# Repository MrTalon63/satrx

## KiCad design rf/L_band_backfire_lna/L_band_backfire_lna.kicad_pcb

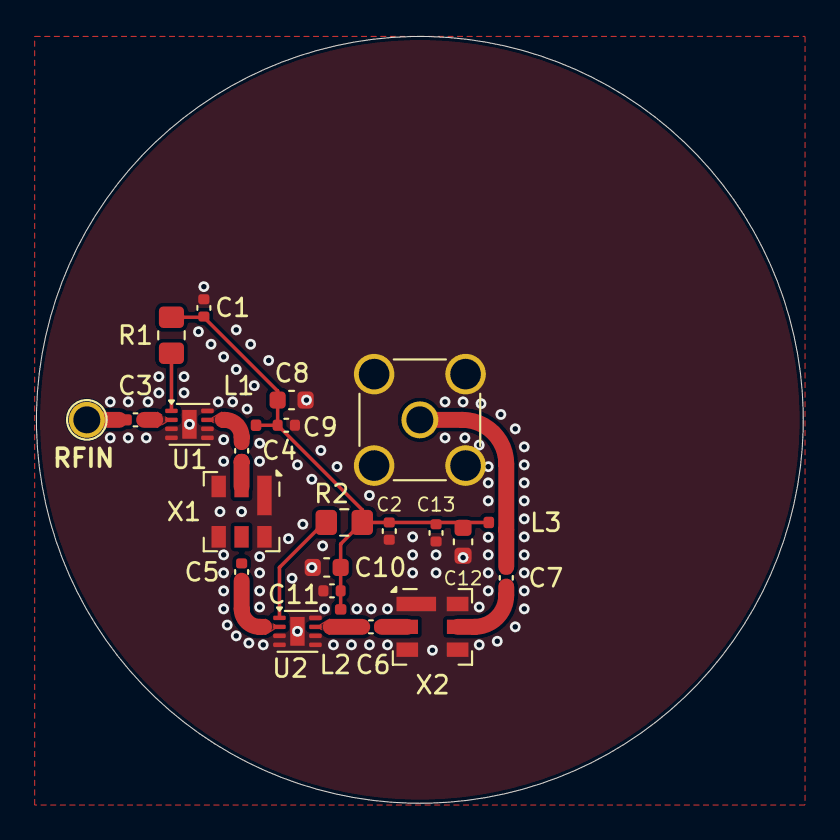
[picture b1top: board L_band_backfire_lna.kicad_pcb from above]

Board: 2 copper layers, 42.6 x 42.6 mm, 24 parts (0 on the bottom side), 14 nets.

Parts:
C1, C2, C3, C4, C5, C6, C7, C9, C11, C13: 100p; C_0402_1005Metric
C8, C10, C12: 100n; C_0603_1608Metric
J1: SMA; Special Hole
J2: SMA; SMA_Amphenol_901-144_Vertical
L1, L2, L3: 56n; L_0402_1005Metric
R1, R2: 3.32k; R_0805_2012Metric_Pad1.20x1.40mm_HandSolder
U1, U2: QPL9547; DFN-8-1EP_2x2mm_P0.5mm_EP0.8x1.6mm
X1, X2: SAW; Filter_SAW-6_3.8x3.8mm

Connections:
GND: C1.2, C2.2, C8.2, C9.1, C10.2, C11.1, C12.2, C13.1, J2.2 (Ext), U1.3 (GND), U1.4 (GND), U1.5 (GND), U1.6 (~EN), U1.8 (GND), U1.9 (GND), U2.3 (GND), U2.4 (GND), U2.5 (GND), U2.6 (~EN), U2.8 (GND), U2.9 (GND), X1.1 (GND), X1.3 (GND), X1.4 (GND), X1.6 (GND), X2.1 (GND), X2.3 (GND), X2.4 (GND), X2.6 (GND)
unnamed: C3.2, U1.2
unnamed: C4.1, L1.1, U1.7
unnamed: C5.2, U2.2
unnamed: C6.1, L2.1, U2.7
unnamed: C3.1, J1.1 (In)
unnamed: C7.2, J2.1 (In), L3.1
unnamed: R1.2, U1.1 (Vb)
unnamed: R2.2, U2.1 (Vb)
unnamed: C4.2, X1.2 (IN)
unnamed: C5.1, X1.5 (OUT)
unnamed: C6.2, X2.2 (IN)
unnamed: C7.1, X2.5 (OUT)
VCC: C1.1, C2.1, C8.1, C9.2, C10.1, C11.2, C12.1, C13.2, L1.2, L2.2, L3.2, R1.1, R2.1

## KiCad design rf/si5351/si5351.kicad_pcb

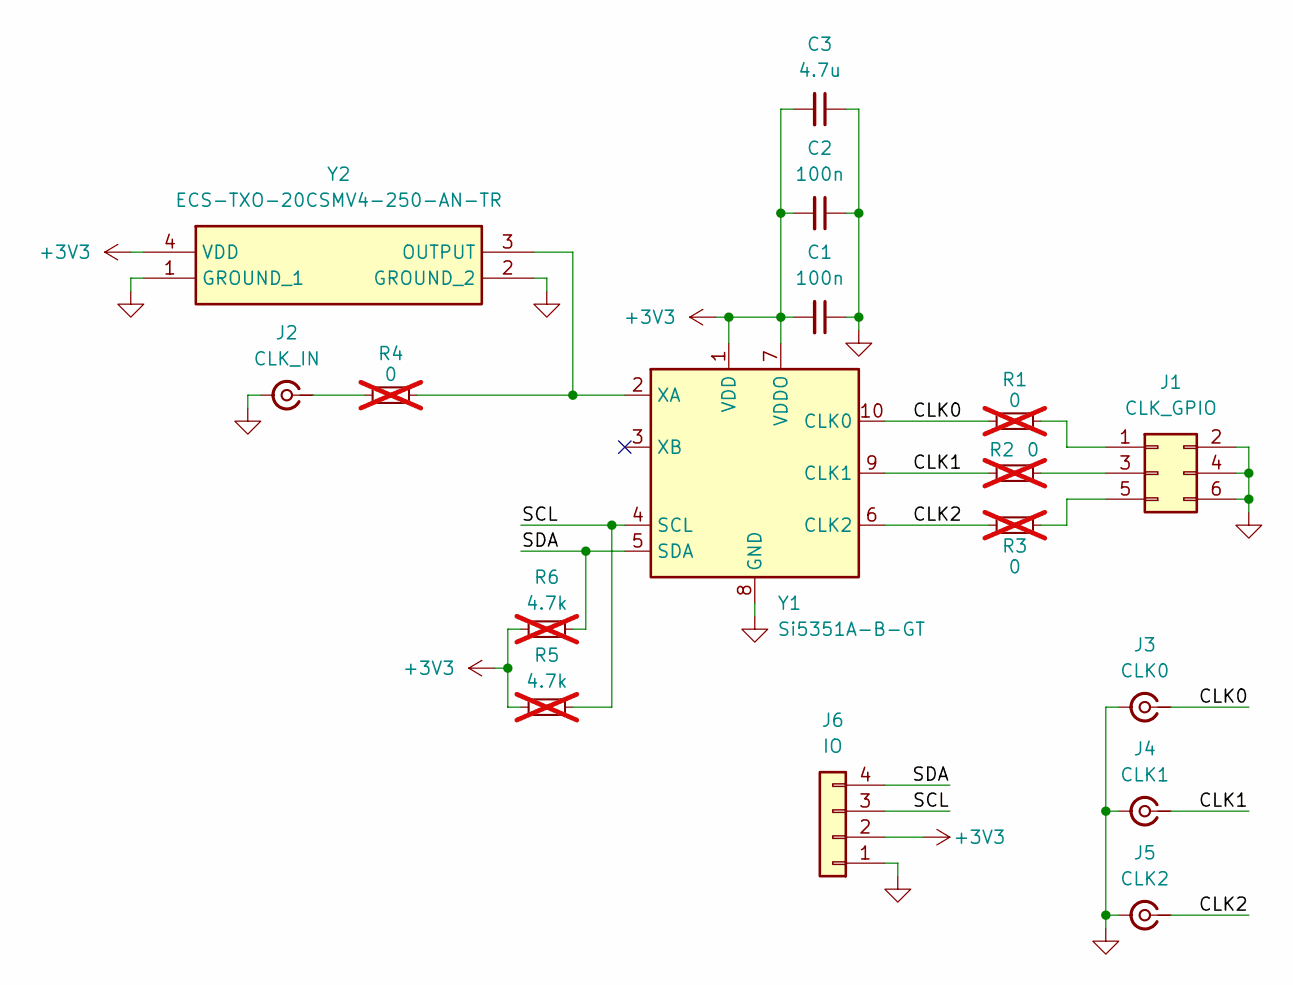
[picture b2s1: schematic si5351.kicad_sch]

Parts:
C1, C2: 100n; C_0603_1608Metric_Pad1.08x0.95mm_HandSolder
C3: 4.7u; C_0603_1608Metric_Pad1.08x0.95mm_HandSolder
J1: CLK_GPIO; PinHeader_2x03_P2.54mm_Vertical
J2: CLK_IN; SMA_Samtec_SMA-J-P-H-ST-EM1_EdgeMount
J3: CLK0; SMA_Samtec_SMA-J-P-H-ST-EM1_EdgeMount
J4: CLK1; SMA_Samtec_SMA-J-P-H-ST-EM1_EdgeMount
J5: CLK2; SMA_Samtec_SMA-J-P-H-ST-EM1_EdgeMount
J6: IO; PinSocket_1x04_P2.54mm_Vertical
R1, R2, R3, R4: 0; R_0603_1608Metric_Pad0.98x0.95mm_HandSolder; not fitted
R5, R6: 4.7k; R_0603_1608Metric_Pad0.98x0.95mm_HandSolder; not fitted
Y1: Si5351A-B-GT; MSOP-10_3x3mm_P0.5mm
Y2: ECS-TXO-20CSMV4-250-AN-TR; ECSTXO20CSMV4250ANTR; Manufacturer_Part_Number ECS-TXO-20CSMV4-250-AN-TR

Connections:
+3V3: C1.2, C2.2, C3.2, J6.2, R5.2, R6.2, Y1.1 (VDD), Y1.7 (VDDO), Y2.4 (VDD)
/CLK0: J3.1 (In), R1.1, Y1.10 (CLK0)
/CLK1: J4.1 (In), R2.1, Y1.9 (CLK1)
/CLK2: J5.1 (In), R3.2, Y1.6 (CLK2)
/SCL: J6.3, R5.1, Y1.4 (SCL)
/SDA: J6.4, R6.1, Y1.5 (SDA)
GND: C1.1, C2.1, C3.1, J1.2, J1.4, J1.6, J2.2 (Ext), J3.2 (Ext), J4.2 (Ext), J5.2 (Ext), J6.1, Y1.8 (GND), Y2.1 (GROUND_1), Y2.2 (GROUND_2)
unnamed: J1.1, R1.2
unnamed: J1.3, R2.2
unnamed: J1.5, R3.1
unnamed: J2.1 (In), R4.1
unnamed: R4.2, Y1.2 (XA), Y2.3 (OUTPUT)

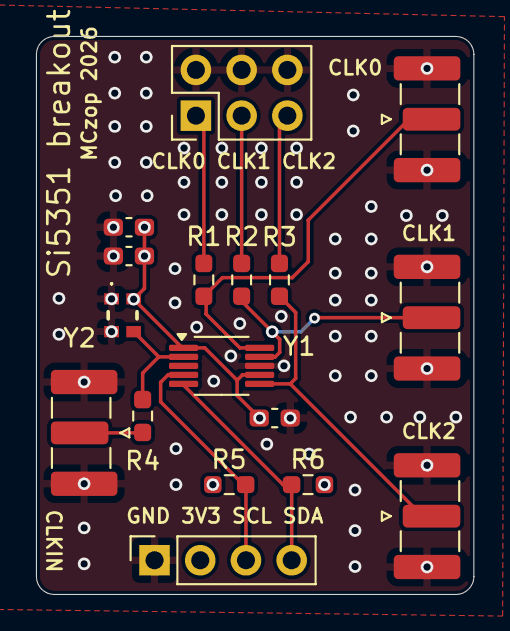
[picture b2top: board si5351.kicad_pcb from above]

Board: 6 copper layers, 24.3 x 31.0 mm, 17 parts (0 on the bottom side), 12 nets.

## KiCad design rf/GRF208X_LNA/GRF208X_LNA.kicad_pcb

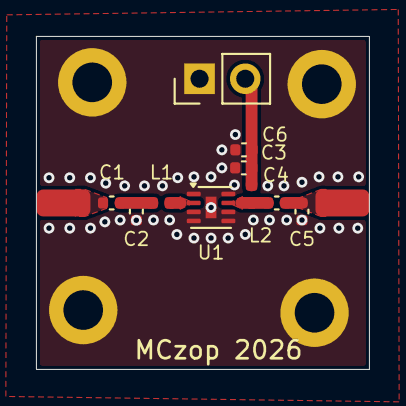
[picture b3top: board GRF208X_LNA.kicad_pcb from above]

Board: 2 copper layers, 18.5 x 18.5 mm, 16 parts (0 on the bottom side), 7 nets.

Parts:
C1: 47p; C_0402_1005Metric
C2, C5, C6: C; C_0402_1005Metric
C3: 100n; C_0402_1005Metric
C4: 18p; C_0402_1005Metric
H1, H2, H3, H4: M2; MountingHole_2.2mm_M2_DIN965_Pad
J1: SMA_IN; SolderWirePad_1x01_SMD_1.5x3mm
J2: SMA_OUT; SolderWirePad_1x01_SMD_1.5x3mm
J3: PWR_IN; PinHeader_1x02_P2.54mm_Vertical
L1: 5.6n; L_0402_1005Metric
L2: 47n; L_0402_1005Metric
U1: GRF208X; DFN-8-1EP_2x2mm_P0.5mm_EP0.6x1.2mm

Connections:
GND: C2.1, C3.1, C5.1, C6.1, H1.1, H2.1, H3.1, H4.1, J3.1, U1.1 (GND), U1.3 (GND), U1.4 (GND), U1.5 (GND), U1.6 (SHTDWN), U1.8 (GND), U1.9 (GND)
unnamed: C1.2, C2.2, L1.1
unnamed: C1.1, J1.1 (In)
unnamed: C4.2, C5.2, J2.1 (In)
unnamed: L1.2, U1.2 (RFIN)
unnamed: C4.1, L2.2, U1.7 (RFOUT)
VDD: C3.2, C6.2, J3.2, L2.1

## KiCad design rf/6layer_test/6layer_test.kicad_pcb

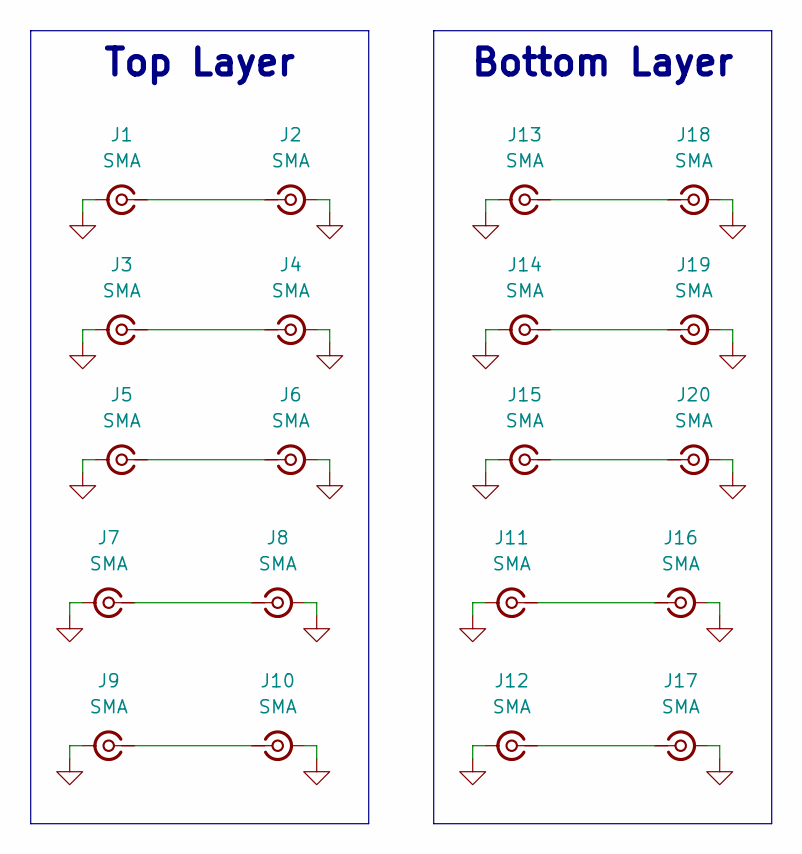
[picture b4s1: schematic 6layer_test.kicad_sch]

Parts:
J1, J2, J3, J4, J5, J6, J7, J8, J9, J10, J11, J12, J13, J14, J15, J16, J17, J18, J19, J20: SMA; SMA_Samtec_SMA-J-P-H-ST-EM1_EdgeMount

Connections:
GND: J1.2 (Ext), J2.2 (Ext), J3.2 (Ext), J4.2 (Ext), J5.2 (Ext), J6.2 (Ext), J7.2 (Ext), J8.2 (Ext), J9.2 (Ext), J10.2 (Ext), J11.2 (Ext), J12.2 (Ext), J13.2 (Ext), J14.2 (Ext), J15.2 (Ext), J16.2 (Ext), J17.2 (Ext), J18.2 (Ext), J19.2 (Ext), J20.2 (Ext)
unnamed: J1.1 (In), J2.1 (In)
unnamed: J3.1 (In), J4.1 (In)
unnamed: J5.1 (In), J6.1 (In)
unnamed: J7.1 (In), J8.1 (In)
unnamed: J9.1 (In), J10.1 (In)
unnamed: J11.1 (In), J16.1 (In)
unnamed: J12.1 (In), J17.1 (In)
unnamed: J13.1 (In), J18.1 (In)
unnamed: J14.1 (In), J19.1 (In)
unnamed: J15.1 (In), J20.1 (In)

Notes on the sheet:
Bottom Layer
Top Layer

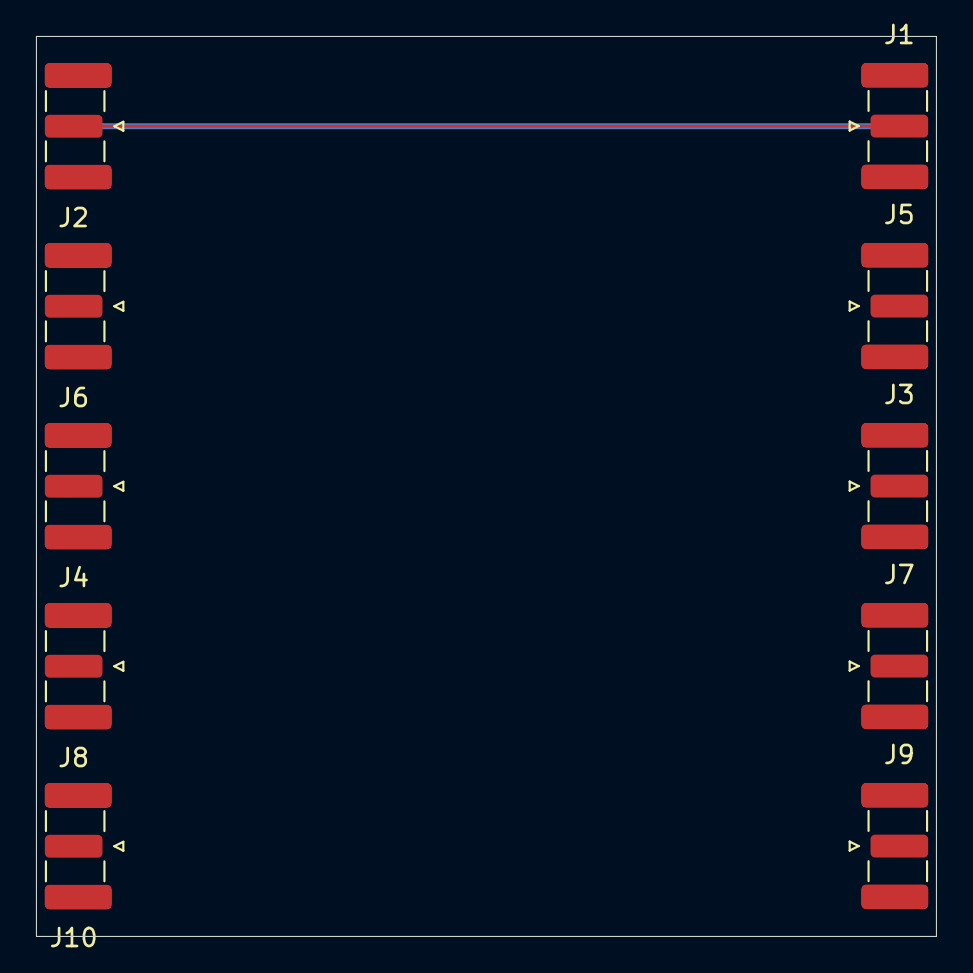
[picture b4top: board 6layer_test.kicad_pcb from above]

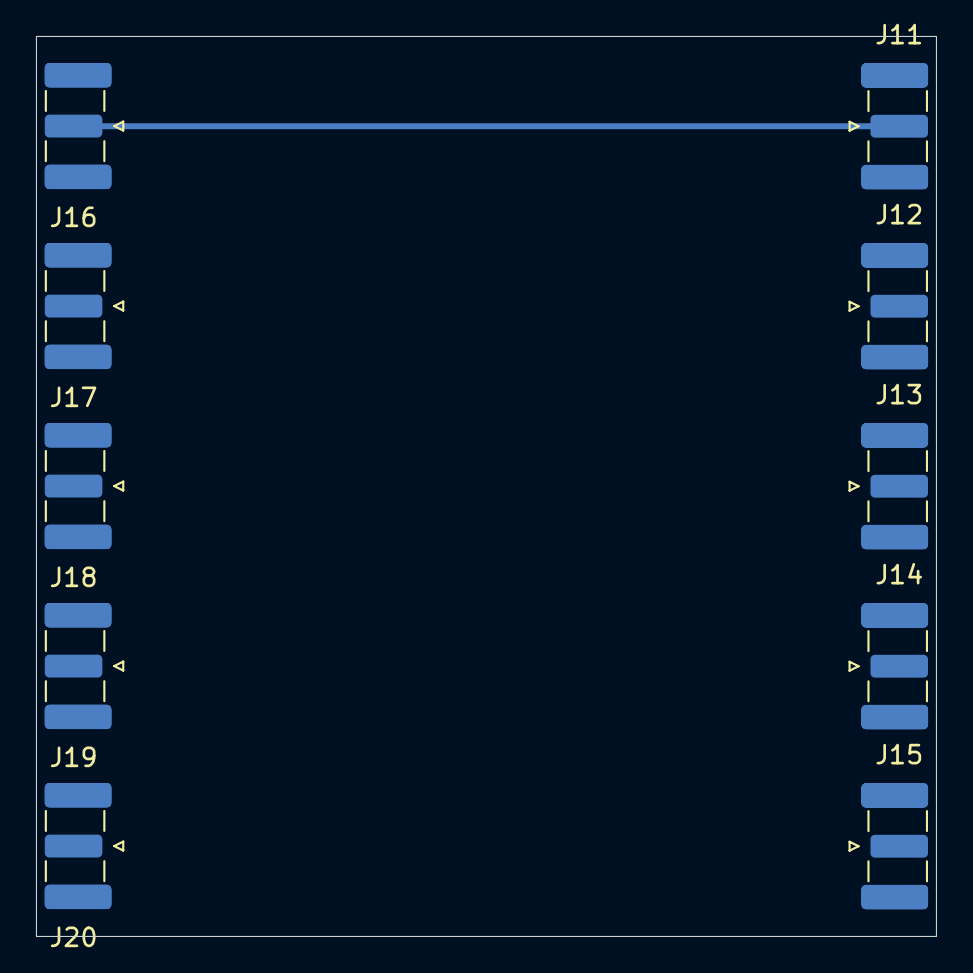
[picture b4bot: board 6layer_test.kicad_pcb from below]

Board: 2 copper layers, 50.0 x 50.0 mm, 20 parts (10 on the bottom side), 11 nets.

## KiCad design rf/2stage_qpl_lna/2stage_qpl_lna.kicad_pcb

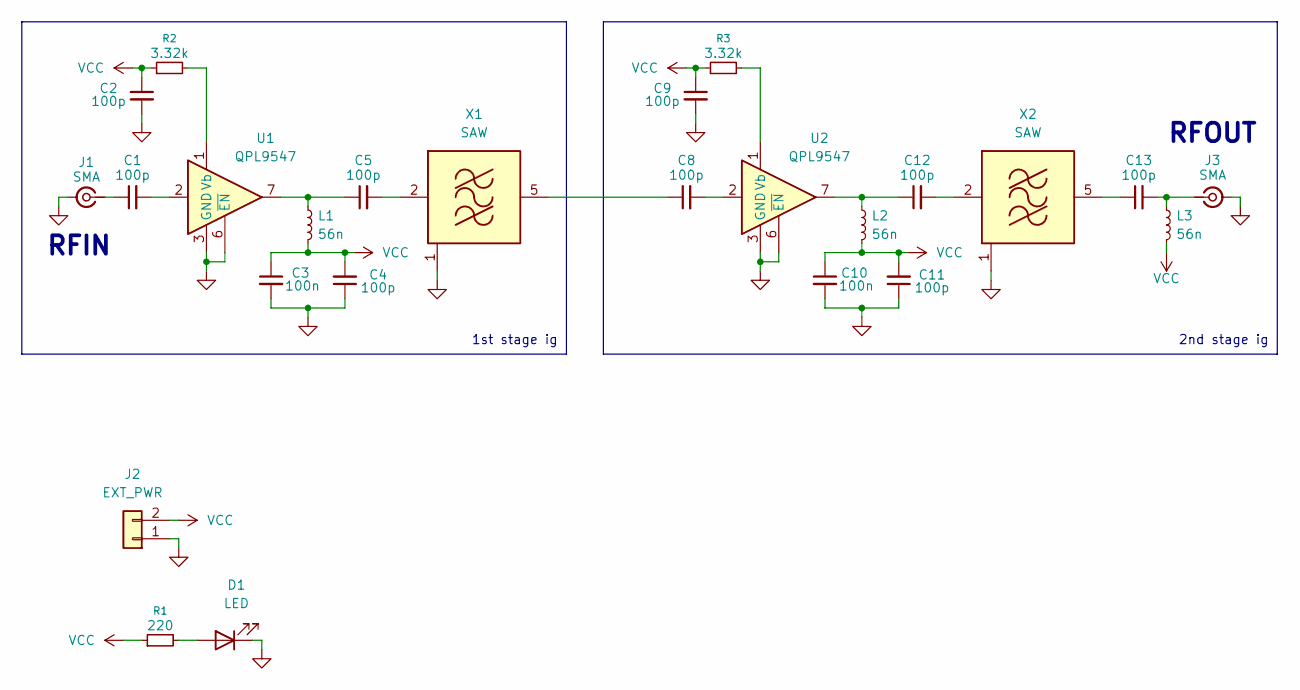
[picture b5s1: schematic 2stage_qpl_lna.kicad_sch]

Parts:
C1, C2, C4, C5, C8, C9, C11, C12, C13: 100p; C_0402_1005Metric
C3, C10: 100n; C_0603_1608Metric_Pad1.08x0.95mm_HandSolder
D1: LED; LED_0603_1608Metric
J1, J3: SMA; SMA_Samtec_SMA-J-P-H-ST-EM1_EdgeMount
J2: EXT_PWR; PinHeader_1x02_P2.54mm_Vertical
L1, L2, L3: 56n; L_0402_1005Metric
R1: 220; R_0603_1608Metric_Pad0.98x0.95mm_HandSolder
R2, R3: 3.32k; R_0402_1005Metric
U1, U2: QPL9547; DFN-8-1EP_2x2mm_P0.5mm_EP0.8x1.6mm
X1, X2: SAW; Filter_SAW-6_3.8x3.8mm

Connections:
GND: C2.2, C3.2, C4.1, C9.2, C10.2, C11.1, D1.1 (K), J1.2 (Ext), J2.1, J3.2 (Ext), U1.3 (GND), U1.4 (GND), U1.5 (GND), U1.6 (~EN), U1.8 (GND), U1.9 (GND), U2.3 (GND), U2.4 (GND), U2.5 (GND), U2.6 (~EN), U2.8 (GND), U2.9 (GND), X1.1 (GND), X1.3 (GND), X1.4 (GND), X1.6 (GND), X2.1 (GND), X2.3 (GND), X2.4 (GND), X2.6 (GND)
unnamed: C1.2, U1.2
unnamed: C5.1, L1.1, U1.7
unnamed: C8.2, U2.2
unnamed: C12.1, L2.1, U2.7
unnamed: D1.2 (A), R1.2
unnamed: C1.1, J1.1 (In)
unnamed: C13.2, J3.1 (In), L3.1
unnamed: R2.2, U1.1 (Vb)
unnamed: R3.2, U2.1 (Vb)
unnamed: C5.2, X1.2 (IN)
unnamed: C8.1, X1.5 (OUT)
unnamed: C12.2, X2.2 (IN)
unnamed: C13.1, X2.5 (OUT)
VCC: C2.1, C3.1, C4.2, C9.1, C10.1, C11.2, J2.2, L1.2, L2.2, L3.2, R1.1, R2.1, R3.1

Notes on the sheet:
RFOUT
1st stage ig
RFIN
2nd stage ig

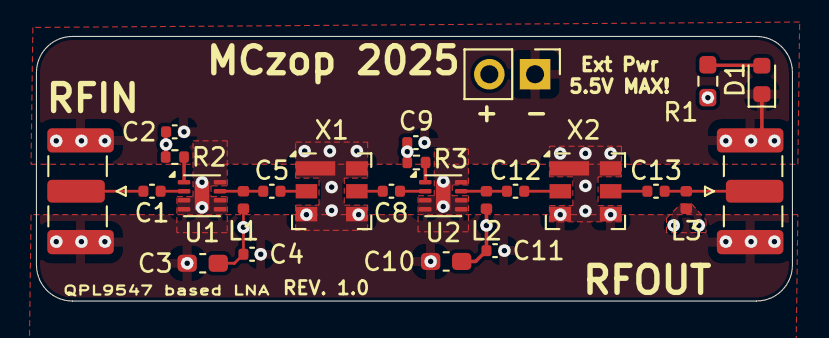
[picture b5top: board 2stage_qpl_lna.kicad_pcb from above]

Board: 6 copper layers, 42.0 x 14.7 mm, 25 parts (0 on the bottom side), 15 nets.

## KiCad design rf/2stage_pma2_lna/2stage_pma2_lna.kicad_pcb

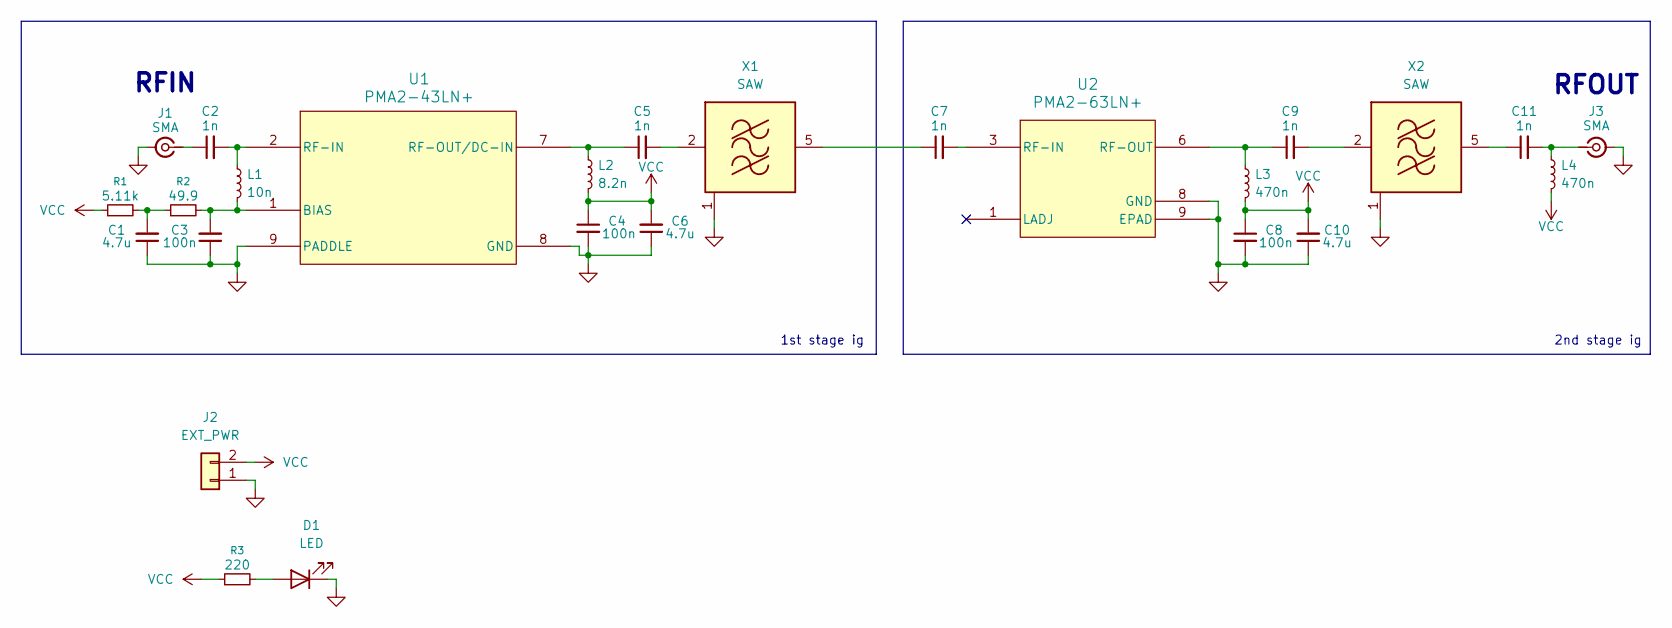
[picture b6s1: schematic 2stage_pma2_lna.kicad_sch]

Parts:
C1, C6, C10: 4.7u; C_0603_1608Metric_Pad1.08x0.95mm_HandSolder
C2, C5, C7, C9, C11: 1n; C_0603_1608Metric_Pad1.08x0.95mm_HandSolder
C3, C4, C8: 100n; C_0603_1608Metric_Pad1.08x0.95mm_HandSolder
D1: LED; LED_D5.0mm_Clear
J1, J3: SMA; SMA_Samtec_SMA-J-P-H-ST-EM1_EdgeMount
J2: EXT_PWR; PinHeader_1x02_P2.54mm_Vertical
L1: 10n; L_0603_1608Metric_Pad1.05x0.95mm_HandSolder
L2: 8.2n; L_0603_1608Metric_Pad1.05x0.95mm_HandSolder
L3, L4: 470n; L_0603_1608Metric_Pad1.05x0.95mm_HandSolder
R1: 5.11k; R_0603_1608Metric_Pad0.98x0.95mm_HandSolder
R2: 49.9; R_0603_1608Metric_Pad0.98x0.95mm_HandSolder
R3: 220; R_0603_1608Metric_Pad0.98x0.95mm_HandSolder
U1: PMA2-43LN+; SON_MC1631-1_MNC
U2: PMA2-63LN+; SON8_PMA2_MNC
X1, X2: SAW; Filter_SAW-6_3.8x3.8mm

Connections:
GND: C1.1, C3.1, C4.2, C6.1, C8.2, C10.1, D1.1 (K), J1.2 (Ext), J2.1, J3.2 (Ext), U1.3 (GND), U1.4 (GND), U1.5 (GND), U1.6 (GND), U1.8 (GND), U1.9 (PADDLE), U2.2 (GND), U2.4 (GND), U2.5 (GND), U2.7 (GND), U2.8 (GND), U2.9 (EPAD), X1.1 (GND), X1.3 (GND), X1.4 (GND), X1.6 (GND), X2.1 (GND), X2.3 (GND), X2.4 (GND), X2.6 (GND)
unnamed: C1.2, R1.2, R2.1
unnamed: D1.2 (A), R3.2
unnamed: C2.1, J1.1 (In)
unnamed: C11.2, J3.1 (In), L4.1
unnamed: C3.2, L1.2, R2.2, U1.1 (BIAS)
unnamed: C2.2, L1.1, U1.2 (RF-IN)
unnamed: C5.1, L2.1, U1.7 (RF-OUT/DC-IN)
unnamed: C7.2, U2.3 (RF-IN)
unnamed: C9.1, L3.1, U2.6 (RF-OUT)
unnamed: C5.2, X1.2 (IN)
unnamed: C7.1, X1.5 (OUT)
unnamed: C9.2, X2.2 (IN)
unnamed: C11.1, X2.5 (OUT)
VCC: C4.1, C6.2, C8.1, C10.2, J2.2, L2.2, L3.2, L4.2, R1.1, R3.1

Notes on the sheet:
RFOUT
1st stage ig
RFIN
2nd stage ig

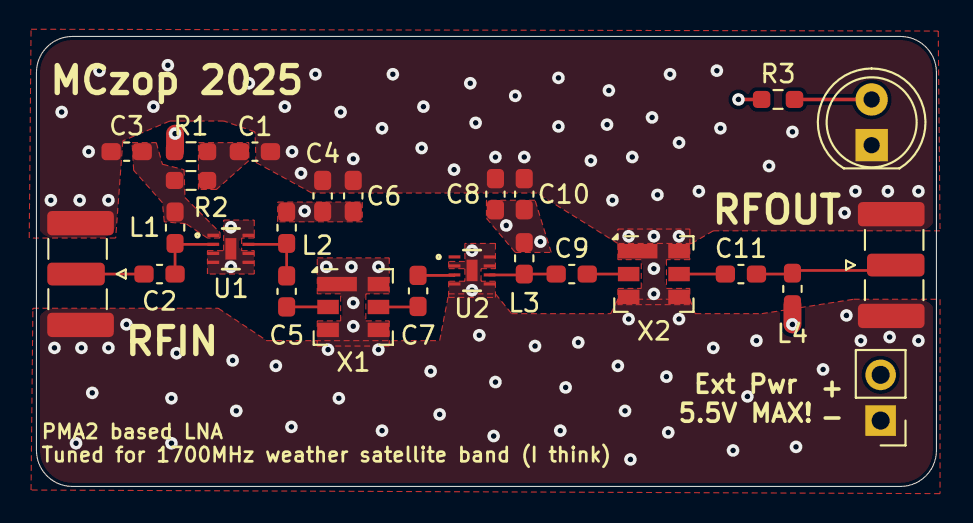
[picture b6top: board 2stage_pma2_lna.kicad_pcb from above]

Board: 6 copper layers, 50.0 x 25.0 mm, 26 parts (0 on the bottom side), 15 nets.

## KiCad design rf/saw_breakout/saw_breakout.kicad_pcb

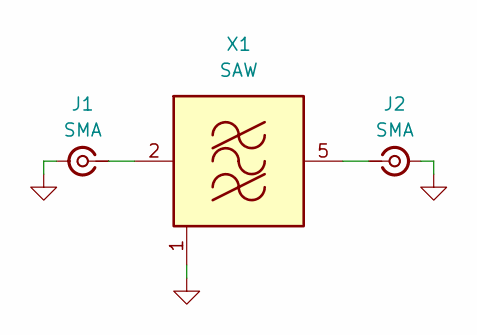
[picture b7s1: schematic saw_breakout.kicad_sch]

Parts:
J1, J2: SMA; SMA_Samtec_SMA-J-P-H-ST-EM1_EdgeMount
X1: SAW; Filter_SAW-6_3.8x3.8mm

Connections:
GND: J1.2 (Ext), J2.2 (Ext), X1.1 (GND), X1.3 (GND), X1.4 (GND), X1.6 (GND)
unnamed: J1.1 (In), X1.2 (IN)
unnamed: J2.1 (In), X1.5 (OUT)

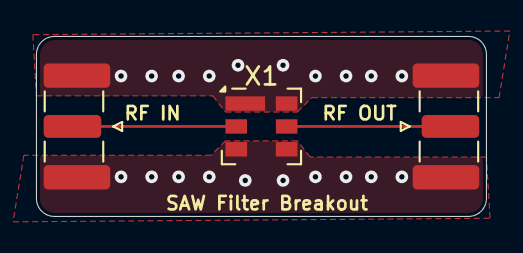
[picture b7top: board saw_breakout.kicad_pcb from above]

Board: 6 copper layers, 25.0 x 10.0 mm, 3 parts (0 on the bottom side), 3 nets.

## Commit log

2025-08-07 SAW breakout and 2 stage LNA schematic
2025-09-03 Update gitignore and PMA2 based LNA files
2025-09-14 Schematic of QPL based 2 stage LNA
2025-09-30 Update QPL based LNA
2025-09-30 Forgor gitignore
2025-12-01 6 layer :thumbsup:
2025-12-02 Gitignore dummy
2025-12-24 Stuff
2026-03-09 Add multiple designs
2026-03-09 Diameter =/= Radius dum dum
2026-03-09 owo what's that :3
2026-03-09 meow
2026-03-09 Make curves smoother
2026-03-27 Satdump api vis
2026-03-27 Add SNR chart and CSV generation
